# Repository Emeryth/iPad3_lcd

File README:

Schematics of an interface board for connecting an iPad retina display (LP097QX1-SPA1) to a DisplayPort source.

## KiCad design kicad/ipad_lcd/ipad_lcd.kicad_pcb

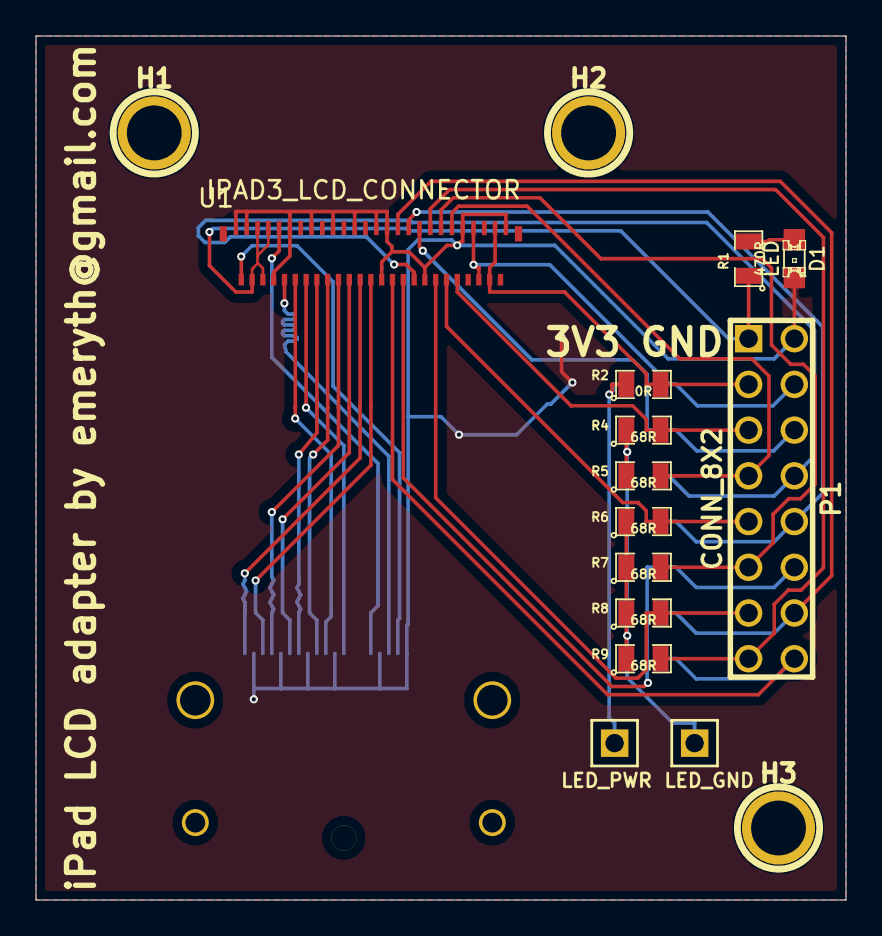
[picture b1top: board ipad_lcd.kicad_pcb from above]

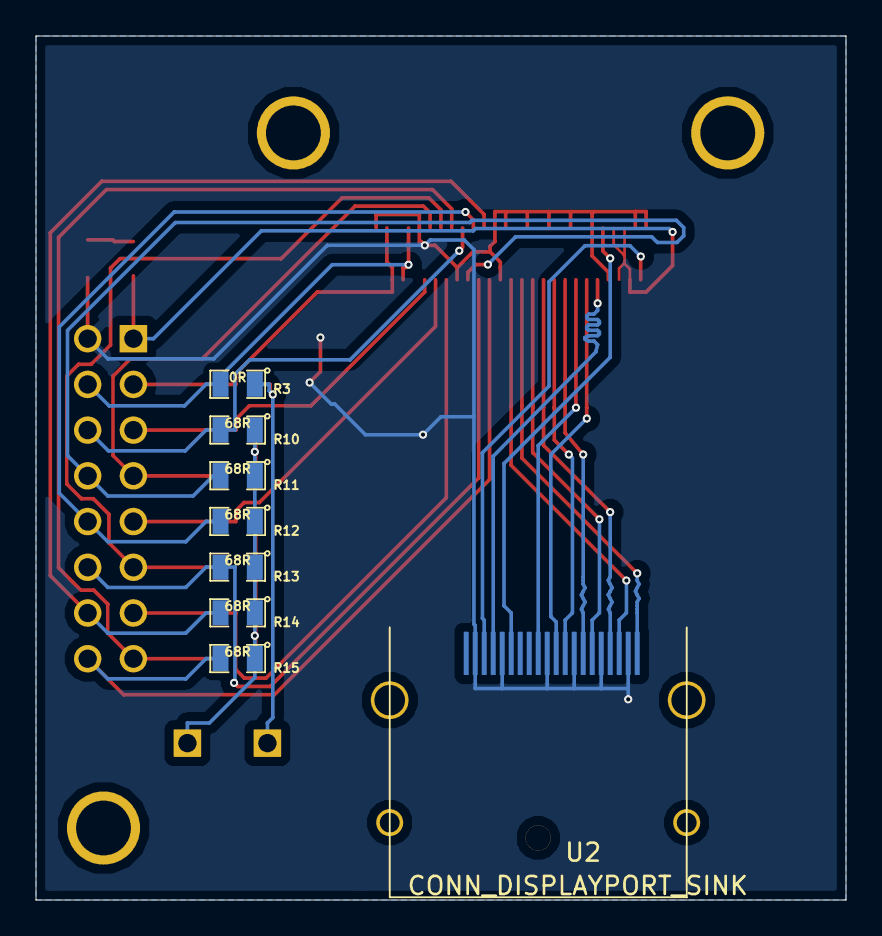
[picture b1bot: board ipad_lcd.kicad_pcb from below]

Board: 2 copper layers, 45.0 x 48.0 mm, 24 parts (8 on the bottom side), 30 nets.

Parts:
D1: LED; LED-0805
H1, H2, H3: P***; 1pin
LED_GND: CONN_1; PIN_ARRAY_1
LED_PWR: CONN_1; PIN_ARRAY_1
P1: CONN_8X2; pin_array_8x2
R1: 470R; SM0805
R2, R3: 0R; SM0805
R4, R5, R6, R7, R8, R9, R10, R11, R12, R13, R14, R15: 68R; SM0805
U1: IPAD3_LCD_CONNECTOR; ipad3_lcd_connector
U2: CONN_DISPLAYPORT_SINK; DP_connector_MC34467

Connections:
+3.3V: P1.1, R1.1, U1.4, U1.5, U1.6, U1.7
/AUX_N: U1.10, U2.17
/AUX_P: U1.9, U2.15
/HPD: U1.2, U2.18
/LANE0_N: U1.12, U2.10
/LANE0_P: U1.14, U2.12
/LANE1_N: U1.16, U2.7
/LANE1_P: U1.18, U2.9
/LANE2_P: U1.22, U2.6
/LANE3_N: U1.24, U2.1
/LANE3_P: U1.26, U2.3
/LANE_2N: U1.20, U2.4
/LEDA_1: P1.3, R2.2, U1.48, U1.49
/LEDA_2: P1.4, R3.2, U1.45, U1.46
/LEDC_1A: P1.5, R4.2, U1.42
/LEDC_1B: P1.6, R10.2, U1.35
/LEDC_2A: P1.7, R5.2, U1.41
/LEDC_2B: P1.8, R11.2, U1.34
/LEDC_3A: P1.9, R6.2, U1.40
/LEDC_3B: P1.10, R12.2, U1.33
/LEDC_4A: P1.11, R7.2, U1.39
/LEDC_4B: P1.12, R13.2, U1.32
/LEDC_5A: P1.13, R8.2, U1.38
/LEDC_5B: P1.14, R14.2, U1.31
/LEDC_6A: P1.15, R9.2, U1.37
/LEDC_6b: P1.16, R15.2, U1.30
/LED_GND: LED_GND.1, R4.1, R5.1, R6.1, R7.1, R8.1, R9.1, R10.1, R11.1, R12.1, R13.1, R14.1, R15.1
/LED_PWR: LED_PWR.1, R2.1, R3.1
GND: D1.2, P1.2, U1.1, U1.3, U1.8, U1.11, U1.15, U1.19, U1.23, U1.27, U1.28, U1.29, U1.36, U1.43, U1.51, U2.2, U2.5, U2.8, U2.11, U2.16, U2.19
unnamed: D1.1, R1.2

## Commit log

2013-04-20 Added readme
2013-05-05 New PCB in Kicad
2013-05-07 Board probably ready
2013-05-07 Changed outline width
2013-05-08 This version sent off to the fab
2013-06-01 Added Kicad design of new PCB. Reorganized the repo.
